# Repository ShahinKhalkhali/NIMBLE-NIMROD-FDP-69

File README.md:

# NIMBLE NIMROD FDP-69
An autonomous drone platform featuring IMU/MPU stabilization, GPS navigation, microphone and speakers, LoRa, Wi-Fi, GSM, USB-C, onboard FPGA acceleration, and eMMC storage. Designed for long-range communication, real-time edge processing, and solar-powered extended missions in research and remote sensing applications.

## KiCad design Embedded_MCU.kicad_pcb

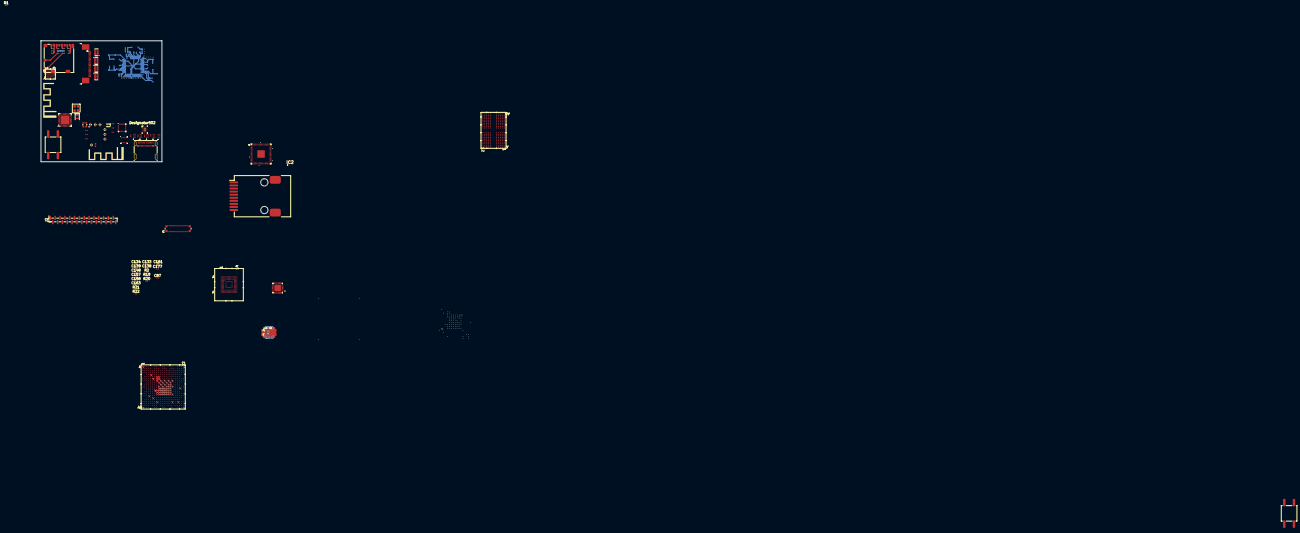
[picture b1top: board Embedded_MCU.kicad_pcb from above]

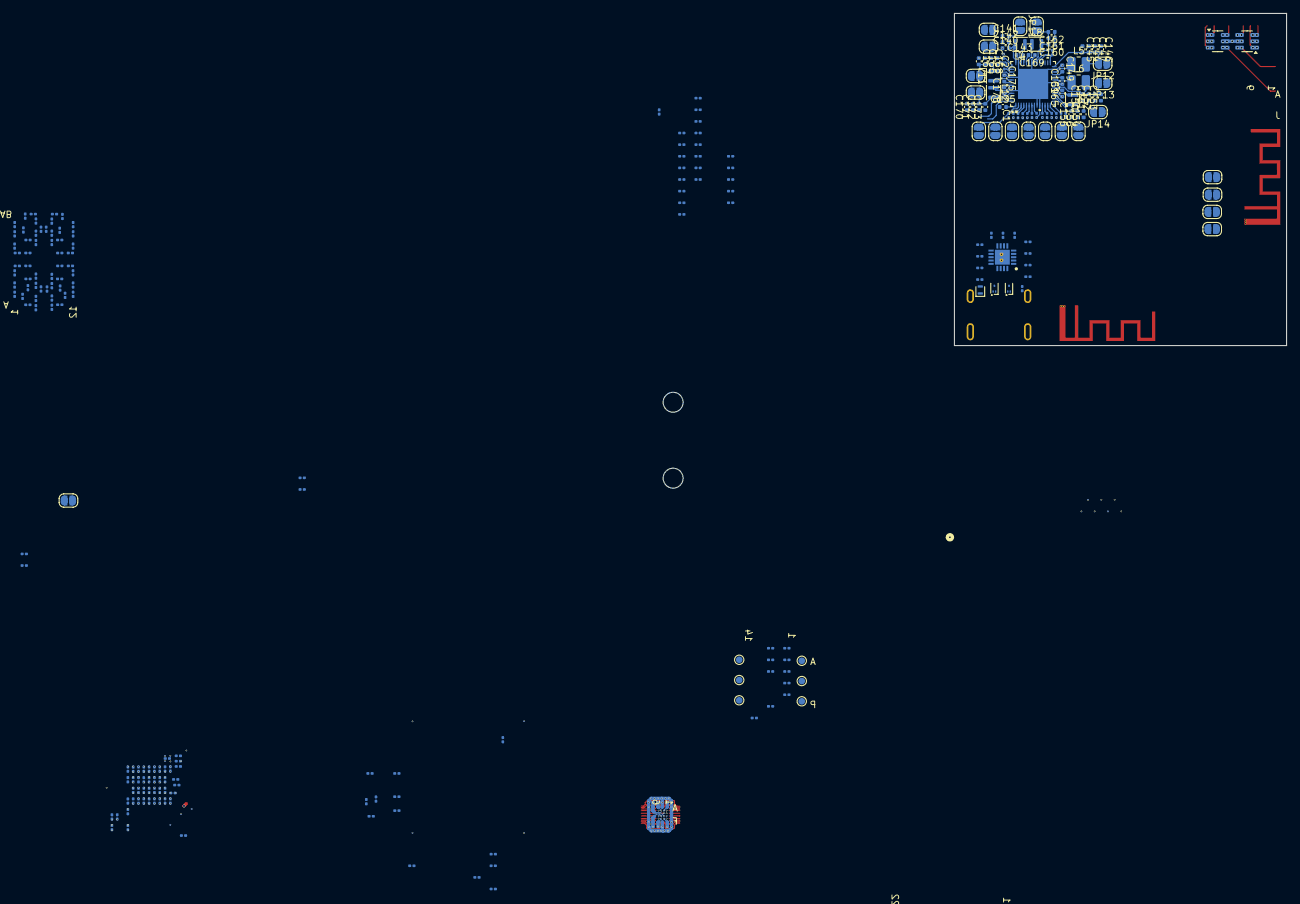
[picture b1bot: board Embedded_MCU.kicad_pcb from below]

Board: 8 copper layers, 50.0 x 50.0 mm, 335 parts (265 on the bottom side), 284 nets.

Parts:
AE1, AE2: Antenna_Shield; 2.4 GHz MIFA
C1, C182, C183, C184, C189: 1u; C_0201_0603Metric
C2, C135, C143, C149, C159, C165, C169, C175, C178, C181: 10u; C_0402_1005Metric
C3, C4, C5, C6, C7, C8, C9, C10, C11, C12, C13, C14, C15, C16, C17, C18, C19, C20, C21, C22, C23, C24, C25, C26, C27, C28, C29, C30, C31, C32, C33, C34, C35, C36, C37, C38, C39, C40, C41, C42, C43, C44, C45, C46, C47, C48, C49, C50, C51, C52, C53, C54, C55, C56, C57, C58, C59, C60, C61, C62, C63, C64, C65, C66, C67, C68, C69, C70, C71, C72, C73, C74, C75, C76, C77, C78, C79, C80, C81, C82, C83, C84, C85, C86, C87, C88, C89, C90, C91, C92, C93, C94, C95, C96, C97, C98, C99, C100, C101, C102, C103, C104, C105, C106, C107, C108, C109, C110, C111, C112, C113, C114, C115, C116, C117, C118, C119, C120, C121, C122, C123, C124, C125, C126, C127, C128, C129, C130, C131, C132, C136, C196, C197, C198, C199, C210: C; C_0201_0603Metric
C133: 4.7U; C_0201_0603Metric
C134, C138, C158, C163, C177, C200, C202, C203, C204, C205, C206: 100n; C_0201_0603Metric
C137, C174, C176, C179, C180, C185, C186, C187, C188: 4.7u; C_0201_0603Metric
C139, C148, C157: 2.2u; C_0201_0603Metric
C140, C141, C142, C144, C145, C146, C147, C150, C151, C152, C153, C154, C155, C156, C160, C161, C162, C166, C167, C168, C170, C171, C172, C173: 22u; C_0402_1005Metric
C201: 10n; C_0201_0603Metric
C207: 10u; C_0201_0603Metric
C208, C209: 470p; C_0201_0603Metric
C216, C219, C222: 100n; C_0402_1005Metric
C217: 1n; C_0402_1005Metric
C218, C220: 10n; C_0402_1005Metric
C221: 470n; C_0402_1005Metric
D5: ESDA25P35-1U1M; ST_QFN-2L_1.6x1.0mm
FB2: 40R @100MHz; L_0402_1005Metric
IC1: TCPP02-M18; QFN50P350X350X60-19N-D
IC2: HSP051-4M10; HSP0514M10
J1: RJ45_Pulse_JXD6-0001NL; RJ45_Pulse_JXD6-0001NL_Horizontal
J2: Conn_01x28_Socket; PinHeader_1x28_P1.00mm_Vertical_SMD_Pin1Right
J4: USB_C_Receptacle_molex; USB_C_Receptacle_Molex_105450-0101
J5: Molex_104031-0811; microSD_HC_Molex_104031-0811
J8: CONN40_AXE540_PAN
J10: Conn_01x22; TE_2-1734839-2_1x22-1MP_P0.5mm_Horizontal
JP6: SolderJumper_3_Open; SolderJumper-2_P1.3mm_Open_RoundedPad1.0x1.5mm
JP7: BOOT0; SolderJumper-2_P1.3mm_Open_RoundedPad1.0x1.5mm
JP8: BOOT1; SolderJumper-2_P1.3mm_Open_RoundedPad1.0x1.5mm
JP9: BOOT2; SolderJumper-2_P1.3mm_Open_RoundedPad1.0x1.5mm
JP10: BOOT3; SolderJumper-2_P1.3mm_Open_RoundedPad1.0x1.5mm
JP11, JP12, JP13, JP14, JP15, JP16, JP17, JP18, JP19, JP20, JP21, JP22, JP23, JP24, JP25, JP26: SolderJumper_2_Open; SolderJumper-2_P1.3mm_Open_RoundedPad1.0x1.5mm
L1: L; L_0201_0603Metric
L4, L11, L12: 0.68u; L_Murata_DFE201610P
L5, L6: 0.68u; L_1008_2520Metric
L7, L8: 2.2u; L_Murata_DFE201610P
L14: 15u; L_0201_0603Metric
Q1, Q2, Q3: NMOS; SOT-1123
R1, R3, R7, R8, R9, R10, R11, R46, R47, R51: R; R_0201_0603Metric
R2, R17, R18, R33, R36, R37, R38: 10k; R_0201_0603Metric
R4, R5, R16: 240; R_0201_0603Metric
R6: 10K; R_0201_0603Metric
R12, R13, R14, R19, R20: 47K; R_0201_0603Metric
R15, R24, R39: 22; R_0201_0603Metric
R21, R22, R23, R25, R26, R27, R28, R31: 47k; R_0201_0603Metric
R34, R35, R40, R41: 200; R_0201_0603Metric
R42, R43: 1.5k; R_0201_0603Metric
R44: 22m; R_0201_0603Metric
R45: 100k; R_0201_0603Metric
R50: 0R; R_0201_0603Metric
SW1, SW2: SW_Push; SW_Push_1P1T_NO_CK_KSC6xxG
TP1: VSF1; TestPoint_Pad_D1.0mm
TP2: VSF2; TestPoint_Pad_D1.0mm
TP3: VSF3; TestPoint_Pad_D1.0mm
TP4: VSF4; TestPoint_Pad_D1.0mm
TP5: VSF5; TestPoint_Pad_D1.0mm
TP6: VSF6; TestPoint_Pad_D1.0mm
U3: ICE40UL1K-CM36AI; ucfBGA36_iCE40Ultra_LAT
U4: ICM-20948; InvenSense_QFN-24_3x3mm_P0.4mm
U5, U22, U23, U24: ECMF04-4HSWM10; UDFN-10_1.35x2.6mm_P0.5mm
U6: ESP32-C3; QFN-32-1EP_5x5mm_P0.5mm_EP3.7x3.7mm
U7: MT53E1G32D2FW-046 IT:B; VFBGA200_10X14.5X1.1FW_MRN
U8: STM32MP255DAI3_func; TFBGA436_STM
U9, U10: USBLC6-4SC6; SOT-23-6
U11: STPMIC25APQR_func_1; WFQFN56L_6p5x6p5x0p9_STM
U13: MTFC32GAZAQHD-WT_func; BGA153_MTFC32_MRN
U14: TUSB542RWQR; RWQ0018A
U15: BME280; Bosch_LGA-8_2.5x2.5mm_P0.65mm_ClockwisePinNumbering
U16: 88E1512-A0-NNP2C000; QFN_56P_MTG
U17, U18, U19, U20, U21: ECMF2-40A100N6; ECMF240A100N6
U26: SX1281IMLTRT; XCVR_SX1281IMLTRT
U28: STA8090WG; BGA_090WG_STM
X1: SMD2520-4; Crystal_SMD_2520-4Pin_2.5x2.0mm
XTAL1: 32.768 KHz; Crystal_SMD_2012-2Pin_2.0x1.2mm
Y2: TG2016SMN_52.0000M-ECGNNM3; OSC_TG2016SMN_52.0000M-ECGNNM3

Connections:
+1V2: C6.1 (+), C7.1 (+), R3.1 (+), U3.D3 (VCC)
+1V8: C11.1, C199.1 (+), C210.1 (+), U3.E4 (SPI_VCCIO1), U4.8 (VDDIO), U4.22 (nCS)
+2V5: C4.1 (+), C5.1 (+), U3.B4 (VPP2V5)
+3V3: C3.1 (+), C10.1, C196.1 (+), C197.1 (+), C198.1 (+), C222.1, FB2.1, R42.2, R43.1, R50.1, R51.2, U3.B3 (VCCIO0), U3.E3 (VCCIO2), U4.13 (VDD), U26.15 (VBAT)
/CSI Connector/CSI_CKN: J8.22, U8.D6 (CSI_CKN)
/CSI Connector/CSI_CKP: J8.24, U8.C6 (CSI_CKP)
/CSI Connector/CSI_D0N: U5.2 (In_1-), U8.B5 (CSI_D0N)
/CSI Connector/CSI_D0P: U5.1 (In_1+), U8.C5 (CSI_D0P)
/CSI Connector/CSI_D1N: U5.5 (In_1-), U8.E7 (CSI_D1N)
/CSI Connector/CSI_D1P: U5.4 (In_1+), U8.D7 (CSI_D1P)
/DSI Connector/DSI_CKN: U8.B8 (DSI_CKN), U23.2 (In_1-)
/DSI Connector/DSI_CKP: U8.A8 (DSI_CKP), U23.1 (In_1+)
/DSI Connector/DSI_D0N: U8.B9 (DSI_D0N), U24.1 (In_1+)
/DSI Connector/DSI_D0P: U8.C9 (DSI_D0P), U24.2 (In_1-)
/DSI Connector/DSI_D1N: U8.E9 (DSI_D1N), U23.5 (In_1-)
/DSI Connector/DSI_D1P: U8.D9 (DSI_D1P), U23.4 (In_1+)
/DSI Connector/DSI_D2N: U8.D8 (DSI_D2N), U22.5 (In_1-)
/DSI Connector/DSI_D2P: U8.C8 (DSI_D2P), U22.4 (In_1+)
/DSI Connector/DSI_D3N: U8.B7 (DSI_D3N), U22.2 (In_1-)
/DSI Connector/DSI_D3P: U8.A7 (DSI_D3P), U22.1 (In_1+)
/FPGA/+1V2_PLL: C8.1 (+), C9.1 (+), R3.2 (-), U3.D4 (VCCPLL)
/FPGA/FPGA_IO0_GBUF6_B2: J2.3, U3.F1 (IOB_0A)
/FPGA/FPGA_IO1_B2: J2.4, U3.E1 (IOB_1B)
/FPGA/FPGA_IO3_GBUF6_B2: J2.2, U3.F2 (IOB_3B_G6)
/FPGA/FPGA_IO4_B2: J2.5, U3.D1 (IOB_4A)
/FPGA/FPGA_IO5_B2: J2.6, U3.C1 (IOB_5B)
/FPGA/FPGA_IO6_B2: J2.19, U3.E2 (IOB_6A)
/FPGA/FPGA_IO7_GBUF5_B2: J2.1, U3.F3 (IOB_7B_G5)
/FPGA/FPGA_IO8_GBUF4_B2: J2.20, U3.D2 (IOB_8A_G4)
/FPGA/FPGA_IO10_B2: J2.16, U3.D6 (IOB_10A)
/FPGA/FPGA_IO11_CFG_PU_CDONE_B2: J2.24, U3.D5 (IOB_11B_CDONE)
/FPGA/FPGA_IO14_SPI_MISOs_MOSIm_B1: J2.26, U3.F6 (IOB_14A_SO)
/FPGA/FPGA_IO15_SPI_MOSIs_MISOm_B1: J2.25, U3.E5 (IOB_15B_SI)
/FPGA/FPGA_IO16_SPI_CLK_B1: J2.17, U3.E6 (IOB_16A_SCK)
/FPGA/FPGA_IO17_SPI_CSn_B1: J2.27, U3.F5 (IOB_17B_SS)
/FPGA/FPGA_IO18_B0: J2.23, U3.B5 (IOT_18B)
/FPGA/FPGA_IO19_B0: J2.11, U3.A4 (IOT_19A)
/FPGA/FPGA_IO21_GBUF1_B0: J2.14, U3.B6 (IOT_21A_G1)
/FPGA/FPGA_IO22_GBUF0_B0: J2.15, U3.C6 (IOT_22B_G0)
/FPGA/FPGA_IO24_B0: J2.22, U3.B2 (IOT_24B)
/FPGA/FPGA_IO25_B0: J2.10, U3.A3 (IOT_25A)
/FPGA/FPGA_IO27_B0: J2.21, U3.C2 (IOT_27A)
/FPGA/FPGA_IOBAR_B0: J2.12, U3.A5 (BARCODE)
/FPGA/FPGA_IOIRLED_B0: J2.13, U3.A6 (IRLED)
/FPGA/FPGA_IORGB0_B0: J2.9, U3.A2 (RGB0)
/FPGA/FPGA_IORGB1_B0: J2.7, U3.B1 (RGB1)
/FPGA/FPGA_IORGB2_B0: J2.8, U3.A1 (RGB2)
/FPGA/FPGA_I_RSTn: J2.28, U3.F4 (CRESET_B)
/LPDDR4/DA0: U7.J4 (CKE0_A), U8.M16 (DDR_A0)
/LPDDR4/DA2: U7.H2 (CA0_A), U8.N16 (DDR_A2)
/LPDDR4/DA3: U7.J2 (CA1_A), U8.M17 (DDR_A3)
/LPDDR4/DA4: U7.J8 (CK_t_A), U8.N19 (DDR_A4)
/LPDDR4/DA5: U7.J9 (CK_c_A), U8.M19 (DDR_A5)
/LPDDR4/DA6: U7.H4 (CS0_A), U8.T18 (DDR_A6)
/LPDDR4/DA8: U7.H9 (CA2_A), U8.P19 (DDR_A8)
/LPDDR4/DA9: U7.H10 (CA3_A), U8.P18 (DDR_A9)
/LPDDR4/DA10: U7.H11 (CA4_A), U8.N18 (DDR_A10)
/LPDDR4/DA11: U7.J11 (CA5_A), U8.N17 (DDR_A11)
/LPDDR4/DA12: U7.P4 (CKE0_B), U8.K19 (DDR_A12)
/LPDDR4/DA14: U7.R2 (CA0_B), U8.L18 (DDR_A14)
/LPDDR4/DA15: U7.P2 (CA1_B), U8.L17 (DDR_A15)
/LPDDR4/DA16: U7.P8 (CK_t_B), U8.J18 (DDR_A16)
/LPDDR4/DA17: U7.P9 (CK_c_B), U8.H18 (DDR_A17)
/LPDDR4/DA18: U7.R4 (CS0_B), U8.H19 (DDR_A18)
/LPDDR4/DA20: U7.R9 (CA2_B), U8.G18 (DDR_A20)
/LPDDR4/DA21: U7.R10 (CA3_B), U8.J19 (DDR_A21)
/LPDDR4/DA22: U7.R11 (CA4_B), U8.H17 (DDR_A22)
/LPDDR4/DA23: U7.P11 (CA5_B), U8.J17 (DDR_A23)
/LPDDR4/DQ0: U7.B2 (DQ0_A), U8.W22 (DDR_DQ0)
/LPDDR4/DQ1: U7.C2 (DQ1_A), U8.Y21 (DDR_DQ1)
/LPDDR4/DQ2: U7.E2 (DQ2_A), U8.Y22 (DDR_DQ2)
/LPDDR4/DQ3: U7.F2 (DQ3_A), U8.AA22 (DDR_DQ3)
/LPDDR4/DQ4: U7.F4 (DQ4_A), U8.T21 (DDR_DQ4)
/LPDDR4/DQ5: U7.E4 (DQ5_A), U8.T20 (DDR_DQ5)
/LPDDR4/DQ6: U7.C4 (DQ6_A), U8.U21 (DDR_DQ6)
/LPDDR4/DQ7: U7.B4 (DQ7_A), U8.U20 (DDR_DQ7)
/LPDDR4/DQ8: U7.B11 (DQ8_A), U8.M21 (DDR_DQ8)
/LPDDR4/DQ9: U7.C11 (DQ9_A), U8.M22 (DDR_DQ9)
/LPDDR4/DQ10: U7.E11 (DQ10_A), U8.L21 (DDR_DQ10)
/LPDDR4/DQ11: U7.F11 (DQ11_A), U8.L22 (DDR_DQ11)
/LPDDR4/DQ12: U7.F9 (DQ12_A), U8.T22 (DDR_DQ12)
/LPDDR4/DQ13: U7.E9 (DQ13_A), U8.R20 (DDR_DQ13)
/LPDDR4/DQ14: U7.C9 (DQ14_A), U8.R21 (DDR_DQ14)
/LPDDR4/DQ15: U7.B9 (DQ15_A), U8.R22 (DDR_DQ15)
/LPDDR4/DQ16: U7.AA2 (DQ0_B), U8.D20 (DDR_DQ16)
/LPDDR4/DQ17: U7.Y2 (DQ1_B), U8.C22 (DDR_DQ17)
/LPDDR4/DQ18: U7.V2 (DQ2_B), U8.C21 (DDR_DQ18)
/LPDDR4/DQ19: U7.U2 (DQ3_B), U8.B22 (DDR_DQ19)
/LPDDR4/DQ20: U7.U4 (DQ4_B), U8.F20 (DDR_DQ20)
/LPDDR4/DQ21: U7.V4 (DQ5_B), U8.F19 (DDR_DQ21)
/LPDDR4/DQ22: U7.Y4 (DQ6_B), U8.E19 (DDR_DQ22)
/LPDDR4/DQ23: U7.AA4 (DQ7_B), U8.E20 (DDR_DQ23)
/LPDDR4/DQ24: U7.AA11 (DQ8_B), U8.G19 (DDR_DQ24)
/LPDDR4/DQ25: U7.Y11 (DQ9_B), U8.G22 (DDR_DQ25)
/LPDDR4/DQ26: U7.V11 (DQ10_B), U8.G21 (DDR_DQ26)
/LPDDR4/DQ27: U7.U11 (DQ11_B), U8.G20 (DDR_DQ27)
/LPDDR4/DQ28: U7.U9 (DQ12_B), U8.J21 (DDR_DQ28)
/LPDDR4/DQ29: U7.V9 (DQ13_B), U8.J20 (DDR_DQ29)
/LPDDR4/DQ30: U7.Y9 (DQ14_B), U8.K20 (DDR_DQ30)
/LPDDR4/DQ31: U7.AA9 (DQ15_B), U8.L19 (DDR_DQ31)
/LPDDR4/DQM0: U7.C3 (DMI0_A), U8.W21 (DDR_DQM0)
/LPDDR4/DQM1: U7.C10 (DMI1_A), U8.P20 (DDR_DQM1)
/LPDDR4/DQM2: U7.Y3 (DMI0_B), U8.E21 (DDR_DQM2)
/LPDDR4/DQM3: U7.Y10 (DMI1_B), U8.H20 (DDR_DQM3)
/LPDDR4/DQS0N: U7.E3 (DQS0_c_A), U8.W20 (DDR_DQS0N)
/LPDDR4/DQS0P: U7.D3 (DQS0_t_A), U8.V20 (DDR_DQS0P)
/LPDDR4/DQS1N: U7.E10 (DQS1_c_A), U8.N21 (DDR_DQS1N)
/LPDDR4/DQS1P: U7.D10 (DQS1_t_A), U8.N20 (DDR_DQS1P)
/LPDDR4/DQS2N: U7.V3 (DQS0_c_B), U8.D22 (DDR_DQS2N)
/LPDDR4/DQS2P: U7.W3 (DQS0_t_B), U8.D21 (DDR_DQS2P)
/LPDDR4/DQS3N: U7.V10 (DQS1_c_B), U8.H21 (DDR_DQS3N)
/LPDDR4/DQS3P: U7.W10 (DQS1_t_B), U8.H22 (DDR_DQS3P)
/LPDDR4/RESETN: R6.1 (+), U7.T11 (RESET_n), U8.F18 (DDR_RESETN)
/LPDDR4/VDDI_LPDDR_1V8: C13.1 (+), C14.1 (+), C15.1 (+), C16.1 (+), C17.1 (+), C18.1 (+), C19.1 (+), C20.1 (+), JP20.1 (A), U7.F1 (VDD1), U7.F12 (VDD1), U7.G4 (VDD1), U7.G9 (VDD1), U7.T4 (VDD1), U7.T9 (VDD1), U7.U1 (VDD1), U7.U12 (VDD1)
/LPDDR4/VDDQ: C45.1 (+), C46.1 (+), C47.1 (+), C48.1 (+), C49.1 (+), C50.1 (+), C51.1 (+), C52.1 (+), C53.1 (+), C54.1 (+), C55.1 (+), C56.1 (+), C57.1 (+), C58.1 (+), C59.1 (+), C60.1 (+), C61.1 (+), C62.1 (+), C63.1 (+), C64.1 (+), U7.AA3 (VDDQ), U7.AA5 (VDDQ), U7.AA8 (VDDQ), U7.AA10 (VDDQ), U7.B3 (VDDQ), U7.B5 (VDDQ), U7.B8 (VDDQ), U7.B10 (VDDQ), U7.D1 (VDDQ), U7.D5 (VDDQ), U7.D8 (VDDQ), U7.D12 (VDDQ), U7.F3 (VDDQ), U7.F10 (VDDQ), U7.U3 (VDDQ), U7.U10 (VDDQ), U7.W1 (VDDQ), U7.W5 (VDDQ), U7.W8 (VDDQ), U7.W12 (VDDQ)
/LPDDR4/VDD_DDR_1V1: C21.1 (+), C22.1 (+), C23.1 (+), C24.1 (+), C25.1 (+), C26.1 (+), C27.1 (+), C28.1 (+), C29.1 (+), C30.1 (+), C31.1 (+), C32.1 (+), C33.1 (+), C34.1 (+), C35.1 (+), C36.1 (+), C37.1 (+), C38.1 (+), C39.1 (+), C40.1 (+), C41.1 (+), C42.1 (+), C43.1 (+), C44.1 (+), C102.1 (+), C103.1 (+), C104.1 (+), C105.1 (+), C106.1 (+), C107.1 (+), C108.1 (+), C109.1 (+), JP16.1 (A), R4.2 (-), R5.2 (-), U7.A4 (VDD2), U7.A9 (VDD2), U7.AB4 (VDD2), U7.AB9 (VDD2), U7.F5 (VDD2), U7.F8 (VDD2), U7.G2 (ODT_CA_A), U7.H1 (VDD2), U7.H5 (VDD2), U7.H8 (VDD2), U7.H12 (VDD2), U7.K1 (VDD2), U7.K3 (VDD2), U7.K10 (VDD2), U7.K12 (VDD2), U7.N1 (VDD2), U7.N3 (VDD2), U7.N10 (VDD2), U7.N12 (VDD2), U7.R1 (VDD2), U7.R5 (VDD2), U7.R8 (VDD2), U7.R12 (VDD2), U7.T2 (ODT_CA_B), U7.U5 (VDD2), U7.U8 (VDD2), U8.K15 (VDDQDDR), U8.L14 (VDDQDDR), U8.L16 (VDDQDDR), U8.M15 (VDDQDDR), U8.N14 (VDDQDDR), U8.P15 (VDDQDDR), U8.R14 (VDDQDDR), U8.R16 (VDDQDDR)
/LPDDR4/ZQ0: R5.1 (+), U7.A5 (ZQ0)
/LPDDR4/ZQ1: R4.1 (+), U7.A8 (ZQ1)
/MPU/COMBOPHY_RX1N: U8.AB20 (COMBOPHY_RX1N), U14.14 (RX_AP-)
/MPU/COMBOPHY_RX1P: U8.AA20 (COMBOPHY_RX1P), U14.15 (RX_AP+)
/MPU/COMBOPHY_TX1N: U8.AB19 (COMBOPHY_TX1N), U14.17 (Tx_AP-)
/MPU/COMBOPHY_TX1P: U8.AA19 (COMBOPHY_TX1P), U14.18 (Tx_AP+)
/MPU/PWR_CTRL2: R11.1 (+), U8.T6 (PWR_CPU_ON)
/MPU/PWR_CTRL3: R11.2 (-), U8.T3 (NRSTC1MS), U11.54 (PWRCTRL3)
/MPU/RSTN: C114.2, SW1.2, U8.U3 (NRST)
/MPU/SDMMC1_CK: J5.5 (CLK), R1.1 (+), R2.1 (+), R24.2 (-), U10.6 (I/O4)
/MPU/SDMMC1_CMD: J5.3 (CMD), R13.1 (+), U8.C16 (PE2), U9.4 (I/O3)
/MPU/SDMMC1_D0: J5.7 (DAT0), R14.1 (+), U8.B17 (PE4), U10.1 (I/O1)
/MPU/SDMMC1_D1: J5.8 (DAT1), R20.1 (+), U8.C17 (PE5), U10.3 (I/O2)
/MPU/SDMMC1_D2: J5.1 (DAT2), R19.1 (+), U8.A16 (PE0), U9.3 (I/O2)
/MPU/SDMMC1_D3: J5.2 (DAT3/CD), R12.1 (+), U8.B16 (PE1), U9.1 (I/O1)
/MPU/SDMMC2_CK: R15.2 (-), R36.1 (+), U13.M6 (CLK)
/MPU/SDMMC2_CMD: R37.1 (+), U8.F17 (PE15), U13.M5 (CMD)
/MPU/SDMMC2_D0: R31.1 (+), U8.B19 (PE13), U13.A3 (DAT0)
/MPU/SDMMC2_D1: R21.1 (+), U8.E17 (PE11), U13.A4 (DAT1)
/MPU/SDMMC2_D2: R22.1 (+), U8.C18 (PE8), U13.A5 (DAT2)
/MPU/SDMMC2_D3: R23.1 (+), U8.C19 (PE12), U13.B2 (DAT3)
/MPU/SDMMC2_D4: R25.1 (+), U8.A19 (PE10), U13.B3 (DAT4)
/MPU/SDMMC2_D5: R26.1 (+), U8.D18 (PE9), U13.B4 (DAT5)
/MPU/SDMMC2_D6: R27.1 (+), U8.E16 (PE6), U13.B5 (DAT6)
/MPU/SDMMC2_D7: R28.1 (+), U8.D17 (PE7), U13.B6 (DAT7)
/MPU/UCPD1_CC1: IC1.2 (CC1), U8.T15 (UCPD1_CC1)
/MPU/UCPD1_CC2: IC1.4 (CC2), U8.T17 (UCPD1_CC2)
/MPU/USB3DR_DM: U8.Y17 (USB3DR_DM), U21.6 (D+_out)
/MPU/USB3DR_DP: U8.W17 (USB3DR_DP), U21.5 (D-_out)
/MPU/VDDA18AON_1V8: C87.1 (+), JP18.1 (A), U8.R7 (VDDA18AON), U8.T7 (PDR_ON)
/MPU/VDDCORE_0V82: C80.1 (+), C81.1 (+), C82.1 (+), C83.1 (+), C84.1 (+), C85.1 (+), C86.1 (+), C121.1 (+), C122.1 (+), C123.1 (+), C124.1 (+), C125.1 (+), C126.1 (+), JP12.1 (A), U8.D5 (VDDCSI), U8.F7 (VDDDSI), U8.G7 (VDDLVDS), U8.H7 (VDDCORE), U8.H9 (VDDCORE), U8.J8 (VDDCORE), U8.J10 (VDDCORE), U8.K9 (VDDCORE), U8.K11 (VDDCORE), U8.L10 (VDDCORE), U8.V18 (VDDPCIECLK), U8.V19 (VDDCOMBOPHY), U8.Y19 (VDDCOMBOPHYTX)
/MPU/VDDCPU_0V8: C89.1 (+), C90.1 (+), C91.1 (+), C92.1 (+), C93.1 (+), C94.1 (+), C95.1 (+), JP11.1 (A), U8.H11 (VDDCPU), U8.H13 (VDDCPU), U8.H15 (VDDCPU), U8.J12 (VDDCPU), U8.J14 (VDDCPU), U8.K13 (VDDCPU), U8.L12 (VDDCPU)
/MPU/VDDGPU_0V8: C96.1 (+), C97.1 (+), C98.1 (+), C99.1 (+), C100.1 (+), C101.1 (+), JP13.1 (A), U8.M11 (VDDGPU), U8.M13 (VDDGPU), U8.N10 (VDDGPU), U8.N12 (VDDGPU), U8.P13 (VDDGPU), U8.R12 (VDDGPU)
/MPU/VDDIO_3V3: C70.1 (+), C71.1 (+), C72.1 (+), C73.1 (+), C74.1 (+), C75.1 (+), C129.2 (-), C130.2 (-), JP6.1 (A), JP14.1 (A), R7.1 (+), R8.1 (+), R9.1 (+), R10.1 (+), U8.F8 (VDDIO3), U8.F9 (VDDIO3), U8.G8 (VDDIO4), U8.G9 (VDDIO4), U8.M9 (VDD), U8.N8 (VDD), U8.P9 (VDD), U8.P11 (VDD), U8.R8 (VDD), U8.R10 (VDD)
/MPU/VDDIO_SDCARD_3V3/1V8: C127.2 (-), JP25.1 (A), U8.G10 (VDDIO1)
/MPU/VDD_USB_3V3: C131.2 (-), C132.2 (-), JP21.1 (A), U8.T16 (VDD33UCPD), U8.Y16 (VDD33USB)
/MPU_POWER/I2C7.SCL: R17.2 (-), U11.33 (SCL)
/MPU_POWER/I2C7.SDA: R18.2 (-), U11.34 (SDA)
/MPU_POWER/VBUS: C136.2, U11.12 (VBUS)
/MPU_POWER/VDDIO_3V3_i: C154.2, C155.2, C156.2, JP14.2 (B), L7.2, R17.1 (+), R18.1 (+), U11.17 (VOUT4), U11.29 (VIO)
/MPU_POWER/VDD_AUX_i: C1.2, C170.2, C171.2, C172.2, C173.2, JP17.2 (B), L12.2, U11.3 (LDO78IN), U11.53 (VOUT7)
/MPU_POWER/VDD_SDCARD: C138.2, JP23.1 (A), R1.2 (-), R2.2 (-), R12.2 (-), R13.2 (-), R14.2 (-), R19.2 (-), R20.2 (-), U9.5 (VBUS), U10.5 (VBUS)
/MPU_POWER/VIN: C137.2, C143.2, C149.2, C159.2, C165.2, C169.2, C175.2, C178.2, C182.2, C183.2, C184.2, U11.6 (LDO56IN), U11.11 (VIN), U11.15 (LDO12IN), U11.20 (BUCK4IN), U11.24 (BUCK3IN), U11.25 (BUCK2IN), U11.38 (BUCK5IN), U11.39 (BUCK1IN), U11.43 (LDO3IN), U11.49 (BUCK6IN), U11.50 (BUCK7IN)
/SD Card Connector/SDMMC1_DETA: J5.10 (DET_A), U10.4 (I/O3)
/SD Card Connector/SDMMC1_DETB: J5.9 (DET_B), U9.6 (I/O4)
/SD Card Connector/VDD_SD_CARD: C133.2, J5.4 (VDD)
/USB-C Port/TCPP_EN: IC1.1 (EN), R45.1
/USB-C Port/VBUS_DIV: C201.1, R46.1, R47.1
/USB-C Port/VIN: C200.1, IC1.3 (VCC_VCONN)
/eMMC/DS: R38.2 (-), R39.1 (+)
/eMMC/RST_N: R33.1 (+), U13.K5 (RST_N)
/eMMC/VCC: C148.2, C158.2, JP19.1 (A), U13.E6 (VCC), U13.F5 (VCC), U13.J10 (VCC), U13.K9 (VCC)
/eMMC/VCCQ: C67.1 (+), C68.1 (+), C69.1 (+), C76.1 (+), C77.1 (+), C115.1 (+), C116.1 (+), C117.1 (+), C118.1 (+), C119.1 (+), C120.1 (+), C128.2 (-), C134.2, C139.2, JP15.1 (A), L1.2, R21.2 (-), R22.2 (-), R23.2 (-), R25.2 (-), R26.2 (-), R27.2 (-), R28.2 (-), R31.2 (-), R33.2 (-), R36.2 (-), R37.2 (-), U8.C4 (VDDA18LVDS), U8.C7 (VDDA18DSI), U8.F6 (VDDA18CSI), U8.F10 (VDDIO2), U8.G17 (VDDA18PLL1), U8.J16 (VDDA18DDR), U8.K8 (VDDA18PLL2), U8.L8 (VDDA18PLL3), U8.U17 (VDDA18USB), U8.W18 (VDDA18COMBOPHY), U8.Y5 (VREF+), U13.C6 (VCCQ), U13.M4 (VCCQ), U13.N4 (VCCQ), U13.P3 (VCCQ), U13.P5 (VCCQ)
/eMMC/VSS: C148.1, C158.1, U13.A6 (VSS), U13.H10 (VSS), U13.J5 (VSS), U13.K8 (VSS)
/eMMC/VSSQ: C134.1, C139.1, U13.C4 (VSSQ), U13.N2 (VSSQ), U13.N5 (VSSQ), U13.P4 (VSSQ), U13.P6 (VSSQ)
GND: C3.2 (-), C4.2 (-), C5.2 (-), C6.2 (-), C7.2 (-), C8.2 (-), C9.2 (-), C10.2, C11.2, C12.2, C133.1, C138.1, C196.2 (-), C197.2 (-), C198.2 (-), C199.2 (-), C200.2, C201.2, C202.2, C207.2, C208.2, C209.2, C210.2 (-), C216.2, C218.2, C219.2, C220.2, C221.2, C222.2, D5.2 (A), IC1.10 (GND_1), IC1.14 (GND_2), IC1.15 (I2C_ADD), IC1.19 (GND_3), J4.A1 (GND), J4.A12 (GND), J4.B1 (GND), J4.B12 (GND), J5.6 (VSS), J5.11 (SHIELD), J8.20, J8.26, J8.32, J8.39, J8.40, J10.4, J10.7, J10.10, J10.13, J10.16, J10.19, J10.22, Q3.3 (S), R38.1 (+), R45.2, R46.2, U3.C3 (GND), U3.C4 (GND), U3.C5 (GND_LED), U4.9 (SDO/AD0), U4.11 (FSYNC), U4.18 (GND), U4.20 (RESV_GND), U5.3 (GND), U5.8 (GND), U9.2 (GND), U10.2 (GND), U14.19 (GND), U17.3 (GND), U17.4 (NC), U18.3 (GND), U18.4 (NC), U19.3 (GND), U19.4 (NC), U20.3 (GND), U20.4 (NC), U21.3 (GND), U21.4 (NC), U22.3 (GND), U22.8 (GND), U23.3 (GND), U23.8 (GND), U24.3 (GND), U24.8 (GND), U26.13 (GND__1), U26.20 (GND__2), U26.21 (GND__3), U26.23 (GND__4), U26.24 (GND__5), U26.25 (EXP), Y2.2 (GND)
GNDP: C1.1, C2.1, C135.1, C136.1, C137.1, C140.1, C141.1, C142.1, C143.1, C144.1, C145.1, C146.1, C147.1, C149.1, C150.1, C151.1, C152.1, C153.1, C154.1, C155.1, C156.1, C159.1, C160.1, C161.1, C162.1, C165.1, C166.1, C167.1, C168.1, C169.1, C170.1, C171.1, C172.1, C173.1, C174.1, C175.1, C176.1, C178.1, C179.1, C180.1, C182.1, C183.1, C184.1, C185.1, C186.1, C187.1, C188.1, C189.1, SW2.1, U11.9 (GNDLDO), U11.10 (AGND), U11.18 (PGND4), U11.22 (PGND3), U11.27 (PGND2), U11.36 (PGND5), U11.41 (PGND1), U11.47 (PGND6), U11.52 (PGND7), U11.57 (EPAD)
MDN0_CAM: J8.30, U5.9 (Out_1+)
MDN1_CAM: J8.18, U5.6 (Out_1+)
MDP0_CAM: J8.28, U5.10 (Out_1+)
MDP1_CAM: J8.16, U5.7 (Out_1+)
unnamed: AE1.1 (A), AE1.2 (Shield), U6.1 (LNA_IN)
unnamed: C65.1 (+), JP6.2 (C), U8.P7 (VBAT)
unnamed: C76.2 (-), U8.W5 (VREF-)
unnamed: C77.2 (-), C78.2 (-), C79.2 (-), U8.U7 (VSSA)
unnamed: C78.1 (+), C79.1 (+), L1.1, U8.V7 (VDDA18ADC)
unnamed: C87.2 (-), U8.M7 (VSSAON)
unnamed: C88.1 (+), U8.M8 (V08CAP)
unnamed: C157.1, C163.1, U13.E7 (VSS), U13.G5 (VSS)
unnamed: C207.1, D5.1 (K), IC1.8 (VBUSC), J4.A4 (VBUS), J4.A9 (VBUS), J4.B4 (VBUS), J4.B9 (VBUS), R44.2, R47.2
unnamed: C202.1, IC1.12 (CBIAS)
unnamed: C208.1, IC1.13 (CC1C), J4.A5 (CC1)
unnamed: C209.1, IC1.11 (CC2C), J4.B5 (CC2)
unnamed: IC1.6 (GATE), Q1.2 (G), Q2.2 (G)
unnamed: IC1.9 (ISENSE), Q2.1 (D), R44.1
unnamed: IC1.17 (SCL), R42.1
unnamed: IC1.16 (SDA), R43.2
unnamed: IC1.7 (SRC), Q1.3 (S), Q2.3 (S)
unnamed: J4.B11 (RX1+), U20.2 (D-_in)
unnamed: J4.B10 (RX1-), U20.1 (D+_in)
unnamed: J4.A11 (RX2+), U18.1 (D+_in)
unnamed: J4.A10 (RX2-), U18.2 (D-_in)
unnamed: J4.A2 (TX1+), U19.2 (D-_in)
unnamed: J4.A3 (TX1-), U19.1 (D+_in)
unnamed: J4.B2 (TX2+), U17.1 (D+_in)
unnamed: J4.B3 (TX2-), U17.2 (D-_in)
unnamed: J10.8, U22.10 (Out_1+)
unnamed: J10.9, U22.9 (Out_1+)
unnamed: J10.11, U22.7 (Out_1+)
unnamed: J10.12, U22.6 (Out_1+)
unnamed: J10.14, U23.10 (Out_1+)
unnamed: J10.15, U23.9 (Out_1+)
unnamed: J10.17, U23.7 (Out_1+)
unnamed: J10.18, U23.6 (Out_1+)
unnamed: J10.20, U24.10 (Out_1+)
unnamed: J10.21, U24.9 (Out_1+)
unnamed: JP7.2 (C), JP8.2 (C), U8.R3 (BOOT1), U8.R4 (BOOT0)
unnamed: JP9.2 (C), U8.T2 (BOOT2)
unnamed: JP10.2 (C), U8.T1 (BOOT3)
unnamed: C140.2, C141.2, C142.2, JP11.2 (B), L4.2, U11.42 (VOUT1)
unnamed: C144.2, C145.2, C146.2, C147.2, JP12.2 (B), L5.2, U11.28 (VOUT2)
unnamed: C150.2, C151.2, C152.2, C153.2, JP13.2 (B), L6.2, U11.21 (VOUT3)
unnamed: C160.2, C161.2, C162.2, JP15.2 (B), L8.2, U11.35 (VOUT5)
unnamed: C166.2, C167.2, C168.2, JP16.2 (B), L11.2, U11.46 (VOUT6)
unnamed: C174.2, JP18.2 (B), U11.14 (LDO1OUT)
unnamed: C176.2, JP19.2 (B), U11.16 (LDO2OUT)
unnamed: C2.2, JP20.2 (B), U11.44 (LDO3OUT)
unnamed: C179.2, JP21.2 (B), U11.13 (LDO4OUT)
unnamed: C180.2, JP22.2 (B), U11.7 (LDO5OUT)
unnamed: C185.2, JP23.2 (B), U11.5 (LDO6OUT)
unnamed: C186.2, JP24.2 (B), U11.4 (LDO7OUT)
unnamed: C188.2, JP25.2 (B), U11.2 (LDO8OUT)
unnamed: C189.2, JP26.1 (A), U11.45 (VREFDDR)
unnamed: Q3.1 (D), R51.1, U26.3 (~RESET)
unnamed: R15.1 (+), U8.A20 (PE14)
unnamed: R16.1 (+), U8.K16 (DDR_ZQ)
unnamed: R24.1 (+), U8.D16 (PE3)
unnamed: R34.2 (-), U8.E8 (DSI_REXT)
unnamed: R35.1 (+), U8.E6 (CSI_REXT)
unnamed: R39.2 (-), U13.H5 (DS)
unnamed: R40.2 (-), U8.Y20 (COMBOPHY_REXT)
unnamed: R41.2 (-), U8.V17 (USB3DR_TXRTUNE)
unnamed: C12.1, U4.10 (REGOUT)
unnamed: U6.2 (VDD3P3), U6.3 (VDD3P3)
unnamed: U6.31 (VDDA), U6.32 (VDDA)
unnamed: C111.2, U8.R1 (OSC32_IN), X1.3
unnamed: C110.2, U8.R2 (OSC32_OUT), X1.1
unnamed: C113.2, U8.V3 (OSC_IN), XTAL1.2
unnamed: C112.2, U8.V2 (OSC_OUT), XTAL1.1
unnamed: C187.2, U11.8 (INTLDO)
unnamed: C135.2, SW2.2, U11.1 (PONKEYN)
unnamed: L4.1, U11.40 (VLX1)
unnamed: L5.1, U11.26 (VLX2)
unnamed: L6.1, U11.23 (VLX3)
unnamed: L7.1, U11.19 (VLX4)
unnamed: L8.1, U11.37 (VLX5)
unnamed: L11.1, U11.48 (VLX6)
unnamed: L12.1, U11.51 (VLX7)
unnamed: C157.2, C163.2, U13.C2 (VDDIM)
unnamed: TP1.1, U13.E8 (VSF1)
unnamed: TP2.1, U13.E9 (VSF2)
unnamed: TP3.1, U13.E10 (VSF3)
unnamed: TP4.1, U13.F10 (VSF4)
unnamed: TP5.1, U13.G10 (VSF5)
unnamed: TP6.1, U13.K10 (VSF6)
unnamed: U14.9 (Rx_Con_2+), U18.6 (D+_out)
unnamed: U14.8 (Rx_Con_2-), U18.5 (D-_out)
unnamed: C205.1, U14.6 (Tx_Con_1+)
unnamed: C206.1, U14.7 (Tx_Con_1-)
unnamed: C203.1, U14.12 (Tx_Con_2+)
unnamed: C204.1, U14.11 (Tx_Con_2-)
unnamed: C203.2, U17.6 (D+_out)
unnamed: C204.2, U17.5 (D-_out)
unnamed: C206.2, U19.6 (D+_out)
unnamed: C205.2, U19.5 (D-_out)
unnamed: J4.A7 (D-), J4.B7 (D-), U21.1 (D+_in)
unnamed: J4.A6 (D+), J4.B6 (D+), U21.2 (D-_in)
unnamed: C218.1, C221.1, L14.1, U26.2 (VDD_IN), U26.12 (DCC_FB)
unnamed: L14.2, U26.14 (DCC_SW)
unnamed: C219.1, R50.2, U26.11 (VBAT_IO)
unnamed: C220.1, U26.1 (VR_PA)
unnamed: C217.2, U26.4 (XTA)
unnamed: C217.1, Y2.3 (OUT)
unnamed: C216.1, FB2.2, Y2.4 (VCC)
Rx_Con_1+: U14.2 (Rx_Con_1+), U20.5 (D-_out)
Rx_Con_1-: U14.3 (Rx_Con_1-), U20.6 (D+_out)
VSS: C65.2 (-), C66.2 (-), C67.2 (-), C68.2 (-), C69.2 (-), C70.2 (-), C71.2 (-), C72.2 (-), C73.2 (-), C74.2 (-), C75.2 (-), C80.2 (-), C81.2 (-), C82.2 (-), C83.2 (-), C84.2 (-), C85.2 (-), C86.2 (-), C88.2 (-), C89.2 (-), C90.2 (-), C91.2 (-), C92.2 (-), C93.2 (-), C94.2 (-), C95.2 (-), C96.2 (-), C97.2 (-), C98.2 (-), C99.2 (-), C100.2 (-), C101.2 (-), C102.2 (-), C103.2 (-), C104.2 (-), C105.2 (-), C106.2 (-), C107.2 (-), C108.2 (-), C109.2 (-), C110.1, C111.1, C112.1, C113.1, C114.1, C115.2 (-), C116.2 (-), C117.2 (-), C118.2 (-), C119.2 (-), C120.2 (-), C121.2 (-), C122.2 (-), C123.2 (-), C124.2 (-), C125.2 (-), C126.2 (-), C127.1 (+), C128.1 (+), C129.1 (+), C130.1 (+), C131.1 (+), C132.1 (+), JP7.1 (A), JP8.1 (A), JP9.1 (A), JP10.1 (A), R16.2 (-), R34.1 (+), R35.2 (-), R40.1 (+), R41.1 (+), SW1.1, U8.A1 (VSS), U8.A22 (VSS), U8.AB1 (VSS), U8.AB22 (VSS), U8.E5 (VSS), U8.G6 (VSS), U8.H8 (VSS), U8.H10 (VSS), U8.H12 (VSS), U8.H14 (VSS), U8.H16 (VSS), U8.J9 (VSS), U8.J11 (VSS), U8.J13 (VSS), U8.J15 (VSS), U8.K10 (VSS), U8.K12 (VSS), U8.K14 (VSS), U8.L9 (VSS), U8.L11 (VSS), U8.L13 (VSS), U8.L15 (VSS), U8.M10 (VSS), U8.M12 (VSS), U8.M14 (VSS), U8.M20 (VSS), U8.N7 (VSS), U8.N9 (VSS), U8.N11 (VSS), U8.N13 (VSS), U8.N15 (VSS), U8.P8 (VSS), U8.P10 (VSS), U8.P12 (VSS), U8.P14 (VSS), U8.R9 (VSS), U8.R11 (VSS), U8.R13 (VSS), U8.R15 (VSS), U8.T4 (VSS), U8.U6 (VSS), U8.W8 (VSS), U8.W16 (VSS), U8.W19 (VSS), X1.2, X1.4
VSS2: C13.2 (-), C14.2 (-), C15.2 (-), C16.2 (-), C17.2 (-), C18.2 (-), C19.2 (-), C20.2 (-), C21.2 (-), C22.2 (-), C23.2 (-), C24.2 (-), C25.2 (-), C26.2 (-), C27.2 (-), C28.2 (-), C29.2 (-), C30.2 (-), C31.2 (-), C32.2 (-), C33.2 (-), C34.2 (-), C35.2 (-), C36.2 (-), C37.2 (-), C38.2 (-), C39.2 (-), C40.2 (-), C41.2 (-), C42.2 (-), C43.2 (-), C44.2 (-), C45.2 (-), C46.2 (-), C47.2 (-), C48.2 (-), C49.2 (-), C50.2 (-), C51.2 (-), C52.2 (-), C53.2 (-), C54.2 (-), C55.2 (-), C56.2 (-), C57.2 (-), C58.2 (-), C59.2 (-), C60.2 (-), C61.2 (-), C62.2 (-), C63.2 (-), C64.2 (-), R6.2 (-), U7.A3 (VSS), U7.A10 (VSS), U7.AB3 (VSS), U7.AB5 (VSS), U7.AB8 (VSS), U7.AB10 (VSS), U7.C1 (VSS), U7.C5 (VSS), U7.C8 (VSS), U7.C12 (VSS), U7.D2 (VSS), U7.D4 (VSS), U7.D9 (VSS), U7.D11 (VSS), U7.E1 (VSS), U7.E5 (VSS), U7.E8 (VSS), U7.E12 (VSS), U7.G1 (VSS), U7.G3 (VSS), U7.G5 (VSS), U7.G8 (VSS), U7.G10 (VSS), U7.G12 (VSS), U7.J1 (VSS), U7.J3 (VSS), U7.J10 (VSS), U7.J12 (VSS), U7.K2 (VSS), U7.K4 (VSS), U7.K9 (VSS), U7.K11 (VSS), U7.N2 (VSS), U7.N4 (VSS), U7.N9 (VSS), U7.N11 (VSS), U7.P1 (VSS), U7.P3 (VSS), U7.P10 (VSS), U7.P12 (VSS), U7.T1 (VSS), U7.T3 (VSS), U7.T5 (VSS), U7.T8 (VSS), U7.T10 (VSS), U7.T12 (VSS), U7.V1 (VSS), U7.V5 (VSS), U7.V8 (VSS), U7.V12 (VSS), U7.W2 (VSS), U7.W4 (VSS), U7.W9 (VSS), U7.W11 (VSS), U7.Y1 (VSS), U7.Y5 (VSS), U7.Y8 (VSS), U7.Y12 (VSS)

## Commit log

2025-11-03 Rename project from Blackbird to NIMBLE NIMROD
    Updated project name and description in README.
2025-11-03 Revise project title in README
    Updated project title to include 'FD-69'.
2025-11-03 Update project name from FD-69 to FDP-69
2025-11-03 Add files via upload
    Initialize
